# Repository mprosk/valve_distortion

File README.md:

# Valve Distortion
Eurorack format reimplementation of the Safety Valve from Look Mum No Computer

## Assembly Instructions

**Step 1:** Solder all resistors and diodes. Resistor values are marked on the silkscreen. **Be sure to get the correct orientation of the diodes!**

**Step 2:** Solder the ceramic capacitors. Ceramic capacitor values are marked on the silkscreen, *with the exception of 0.1uF / 100nF which are unlabeled*

**Step 3:** Solder the electrolytic capacitors. Capacitor values are marked on the silkscreen. **Be sure to get the correct polarity of the capacitors!** The white silkscreen fill indicates the negative leg of the capacitor. Capacitors should be folded down as shown above.

**Step 4:** Solder the ICs, transistor, trim pot, and 10pin power connector. **Be sure to get the correct orientation of the ICs!** Match the U shaped indent on the chip to the marking on the IC. The trim pot should be mounted sideways as shown above. The power connector should be mounted on the back of the PCB. **Make sure to get the correct orientation of the connector housing!**

**Step 5:** Place the switches, potentiometers, red 5mm LED, jacks, and tube in their respective locations in the PCB **but do not solder them yet!** First, place the faceplate over the controls and screw on the mounting hardware for each component. Note that due to slight hight differences between the parts, the nuts may not screw down all the way. **Do not over-tighten the mounting hardware as this may cause unwanted flexing of the PCBs.** You can use a rubber band or similar to hold everything together while handling. Push the legs of the LED from the back so that it just sticks through the front panel. Bend the legs from the back to hold it in place. **Be sure you have the correct polarity of the LED.**

**Step 6:** Once all the mounting hardware is secured, solder the switches, tube, LED, jacks, and potentiometers in place.

**Step 7:** Push the 3mm clear LED through the hole on the back of the PCB underneath the tube. Bend the leads such that they reach their connection points and cut them to length. **Be sure you have the correct polarity of the LED!** Solder the LED in place

**Step 8:** Put the knobs on to the potentiometers

**Step 9:** Power the module up and apply a signal to the input. Adjust the trim pot such that the LED underneath the tube illuminates when there is signal but is off when there is not. Note that sometimes the EMC of the LED can get picked up by the tube and cause an audible noise. If this occurs, adjust the trim pot such that the LED does not illuminate regardless of the signal level.

**Step 10:** Enjoy your gnarly new distortion module!

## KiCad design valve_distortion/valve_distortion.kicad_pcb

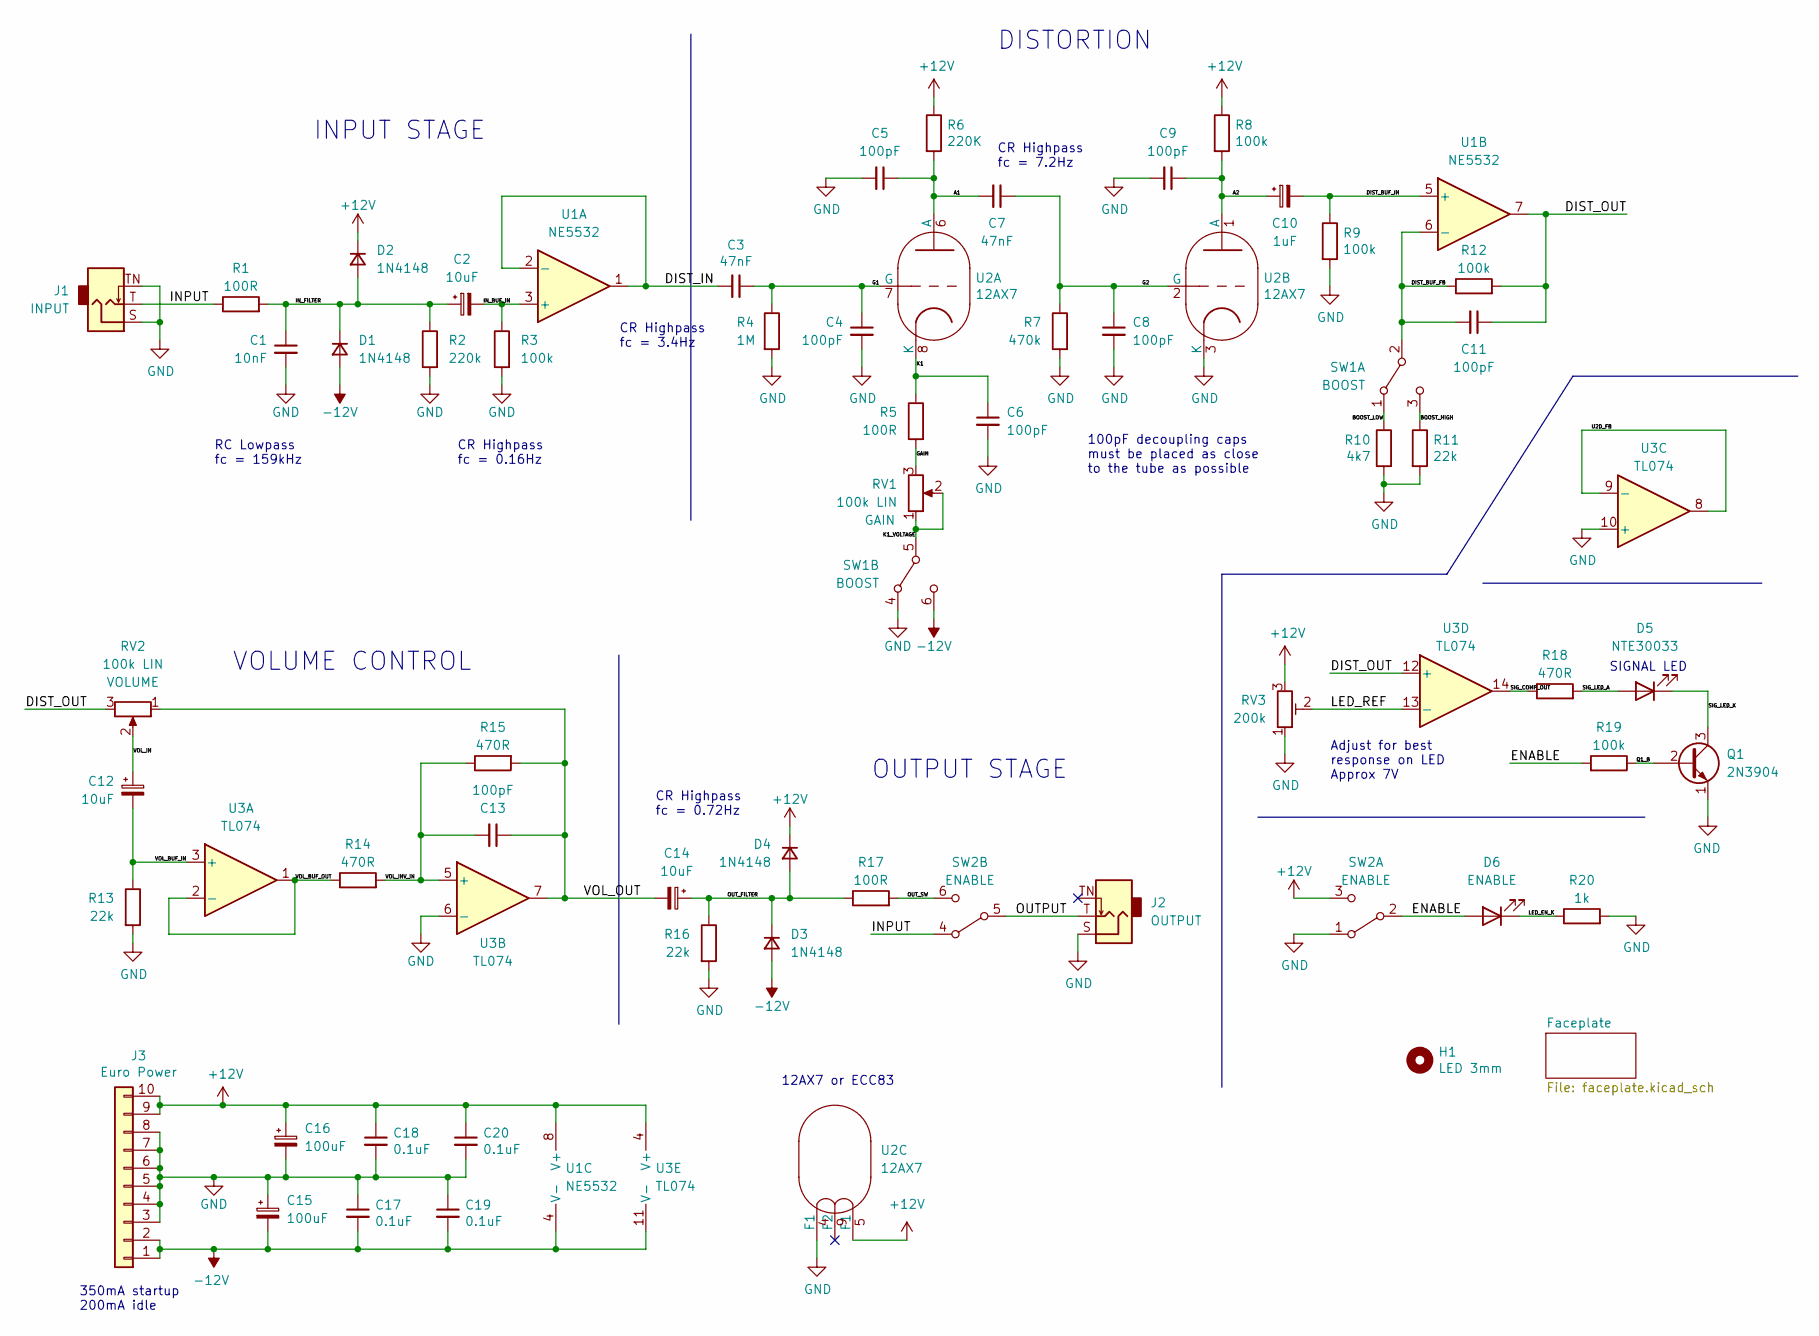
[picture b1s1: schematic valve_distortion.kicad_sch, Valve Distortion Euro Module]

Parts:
C1: 10nF; C_Disc_D4.3mm_W1.9mm_P5.00mm
C2, C12, C14: 10uF; CP_Radial_D5.0mm_P2.50mm
C3, C7: 47nF; C_Disc_D3.0mm_W1.6mm_P2.50mm
C4, C5, C6, C8, C9, C11, C13: 100pF; C_Disc_D3.0mm_W1.6mm_P2.50mm
C10: 1uF; CP_Radial_D5.0mm_P2.50mm
C15, C16: 100uF; CP_Radial_D5.0mm_P2.50mm
C17, C18, C19, C20: 0.1uF; C_Disc_D3.0mm_W1.6mm_P2.50mm
D1, D2, D3, D4: 1N4148; D_DO-34_SOD68_P7.62mm_Horizontal
D5: NTE30033; LED_D3.0mm_Clear
D6: ENABLE; LED_D5.0mm
H1: LED 3mm; Hole_LED_3mm
J1: INPUT; Jack_3.5mm_QingPu_WQP-PJ301BM
J2: OUTPUT; Jack_3.5mm_QingPu_WQP-PJ301BM
J3: Euro Power; IDC-Header_2x05_P2.54mm_Vertical
Q1: 2N3904; TO-92_Inline
R1, R5, R17: 100R; R_Axial_DIN0207_L6.3mm_D2.5mm_P10.16mm_Horizontal
R2: 220k; R_Axial_DIN0207_L6.3mm_D2.5mm_P10.16mm_Horizontal
R3, R8, R9, R12, R19: 100k; R_Axial_DIN0207_L6.3mm_D2.5mm_P10.16mm_Horizontal
R4: 1M; R_Axial_DIN0207_L6.3mm_D2.5mm_P10.16mm_Horizontal
R6: 220K; R_Axial_DIN0207_L6.3mm_D2.5mm_P10.16mm_Horizontal
R7: 470k; R_Axial_DIN0207_L6.3mm_D2.5mm_P10.16mm_Horizontal
R10: 4k7; R_Axial_DIN0207_L6.3mm_D2.5mm_P10.16mm_Horizontal
R11, R13, R16: 22k; R_Axial_DIN0207_L6.3mm_D2.5mm_P10.16mm_Horizontal
R14, R15, R18: 470R; R_Axial_DIN0207_L6.3mm_D2.5mm_P10.16mm_Horizontal
R20: 1k; R_Axial_DIN0207_L6.3mm_D2.5mm_P10.16mm_Horizontal
RV1, RV2: 100k LIN; Potentiometer_TT_P0915N
RV3: 200k; Potentiometer_Trim_Horizontal
SW1: BOOST; Switch_DPDT
SW2: ENABLE; Switch_DPDT
U1: NE5532; DIP-8_W7.62mm
U2: 12AX7; Valve_ECC-83-1
U3: TL074; DIP-14_W7.62mm

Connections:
+12V: C16.1, C18.1, C20.1, D2.1 (K), D4.1 (K), J3.9, J3.10, R6.1, R8.1, RV3.3, SW2.3 (C), U1.8 (V+), U2.5 (F1), U3.4 (V+)
-12V: C15.2, C17.2, C19.2, D1.2 (A), D3.2 (A), J3.1, J3.2, SW1.6 (C), U1.4 (V-), U3.11 (V-)
/A1: C5.1, C7.2, R6.2, U2.6 (A)
/A2: C9.1, C10.1, R8.2, U2.1 (A)
/BOOST_HIGH: R11.1, SW1.3 (C)
/BOOST_LOW: R10.1, SW1.1 (A)
/DIST_BUF_FB: C11.2, R12.1, SW1.2 (B), U1.6 (-)
/DIST_BUF_IN: C10.2, R9.1, U1.5 (+)
/DIST_IN: C3.2, U1.1, U1.2 (-)
/DIST_OUT: C11.1, R12.2, RV2.3, U1.7, U3.12 (+)
/ENABLE: D6.2 (A), R19.2, SW2.2 (B)
/G1: C3.1, C4.1, R4.1, U2.7 (G)
/G2: C7.1, C8.1, R7.1, U2.2 (G)
/GAIN: R5.2, RV1.3
/INPUT: J1.T, R1.1, SW2.4 (A)
/IN_BUF_IN: C2.2, R3.1, U1.3 (+)
/IN_FILTER: C1.1, C2.1, D1.1 (K), D2.2 (A), R1.2, R2.1
/K1: C6.1, R5.1, U2.8 (K)
/K1_VOLTAGE: RV1.1, RV1.2, SW1.5 (B)
/LED_EN_K: D6.1 (K), R20.1
/LED_REF: RV3.2, U3.13 (-)
/OUTPUT: J2.T, SW2.5 (B)
/OUT_FILTER: C14.1, D3.1 (K), D4.2 (A), R16.1, R17.1
/OUT_SW: R17.2, SW2.6 (C)
/Q1_B: Q1.2 (B), R19.1
/SIG_COMP_OUT: R18.1, U3.14
/SIG_LED_A: D5.2 (A), R18.2
/SIG_LED_K: D5.1 (K), Q1.3 (C)
/U2D_FB: U3.8, U3.9 (-)
/VOL_BUF_IN: C12.2, R13.1, U3.3 (+)
/VOL_BUF_OUT: R14.1, U3.1, U3.2 (-)
/VOL_IN: C12.1, RV2.2
/VOL_INV_IN: C13.2, R14.2, R15.1, U3.5 (+)
/VOL_OUT: C13.1, C14.2, R15.2, RV2.1, U3.7
GND: C1.2, C4.2, C5.2, C6.2, C8.2, C9.2, C15.1, C16.2, C17.1, C18.2, C19.1, C20.2, J1.S, J1.TN, J2.S, J3.3, J3.4, J3.5, J3.6, J3.7, J3.8, Q1.1 (E), R2.2, R3.2, R4.2, R7.2, R9.2, R10.2, R11.2, R13.2, R16.2, R20.2, RV3.1, SW1.4 (A), SW2.1 (A), U2.3 (K), U2.4 (F1), U3.6 (-), U3.10 (+)

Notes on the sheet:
CR Highpass fc = 0.16Hz
VOLUME CONTROL
CR Highpass fc = 3.4Hz
12AX7 or ECC83
Adjust for best response on LED Approx 7V
DISTORTION
RC Lowpass fc = 159kHz
CR Highpass fc = 0.72Hz
INPUT STAGE
100pF decoupling caps must be placed as close to the tube as possible
OUTPUT STAGE
CR Highpass fc = 7.2Hz
350mA startup 200mA idle
SIGNAL LED

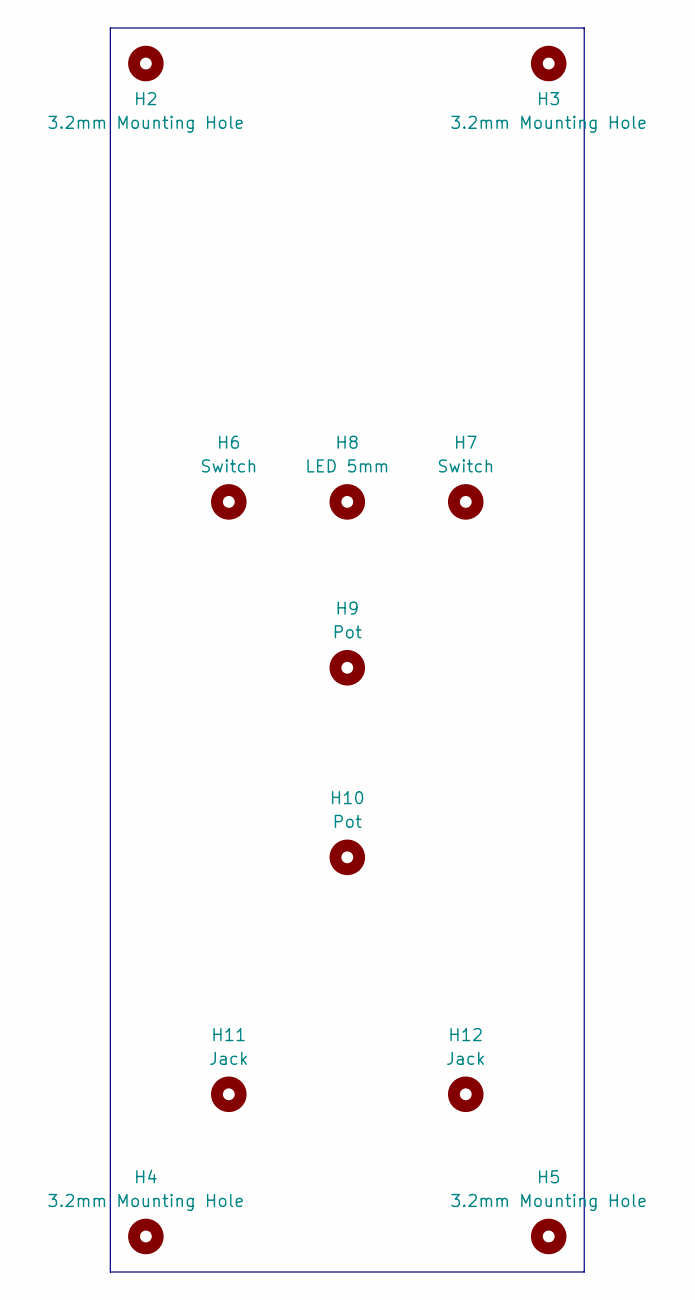
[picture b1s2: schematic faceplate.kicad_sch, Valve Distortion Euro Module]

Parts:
H2, H3, H4, H5: 3.2mm Mounting Hole; MountingHole_3.2mm_M3
H6, H7: Switch; Hole_Toggle_Switch
H8: LED 5mm; Hole_LED_5mm
H9, H10: Pot; Hole_Pot
H11, H12: Jack; Hole_Jack_3.5mm

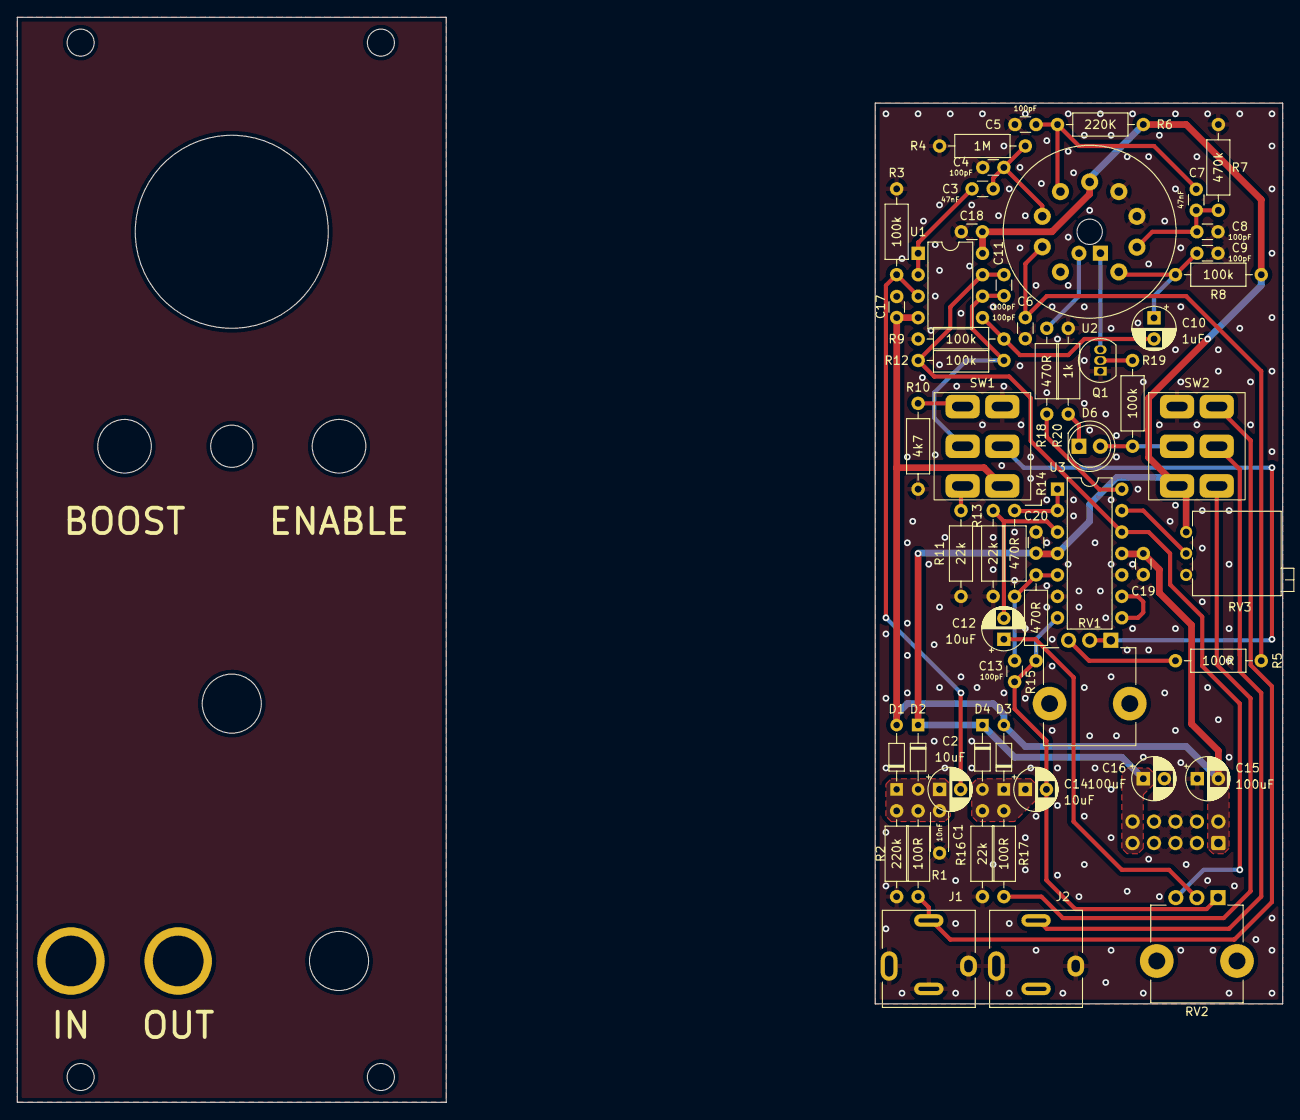
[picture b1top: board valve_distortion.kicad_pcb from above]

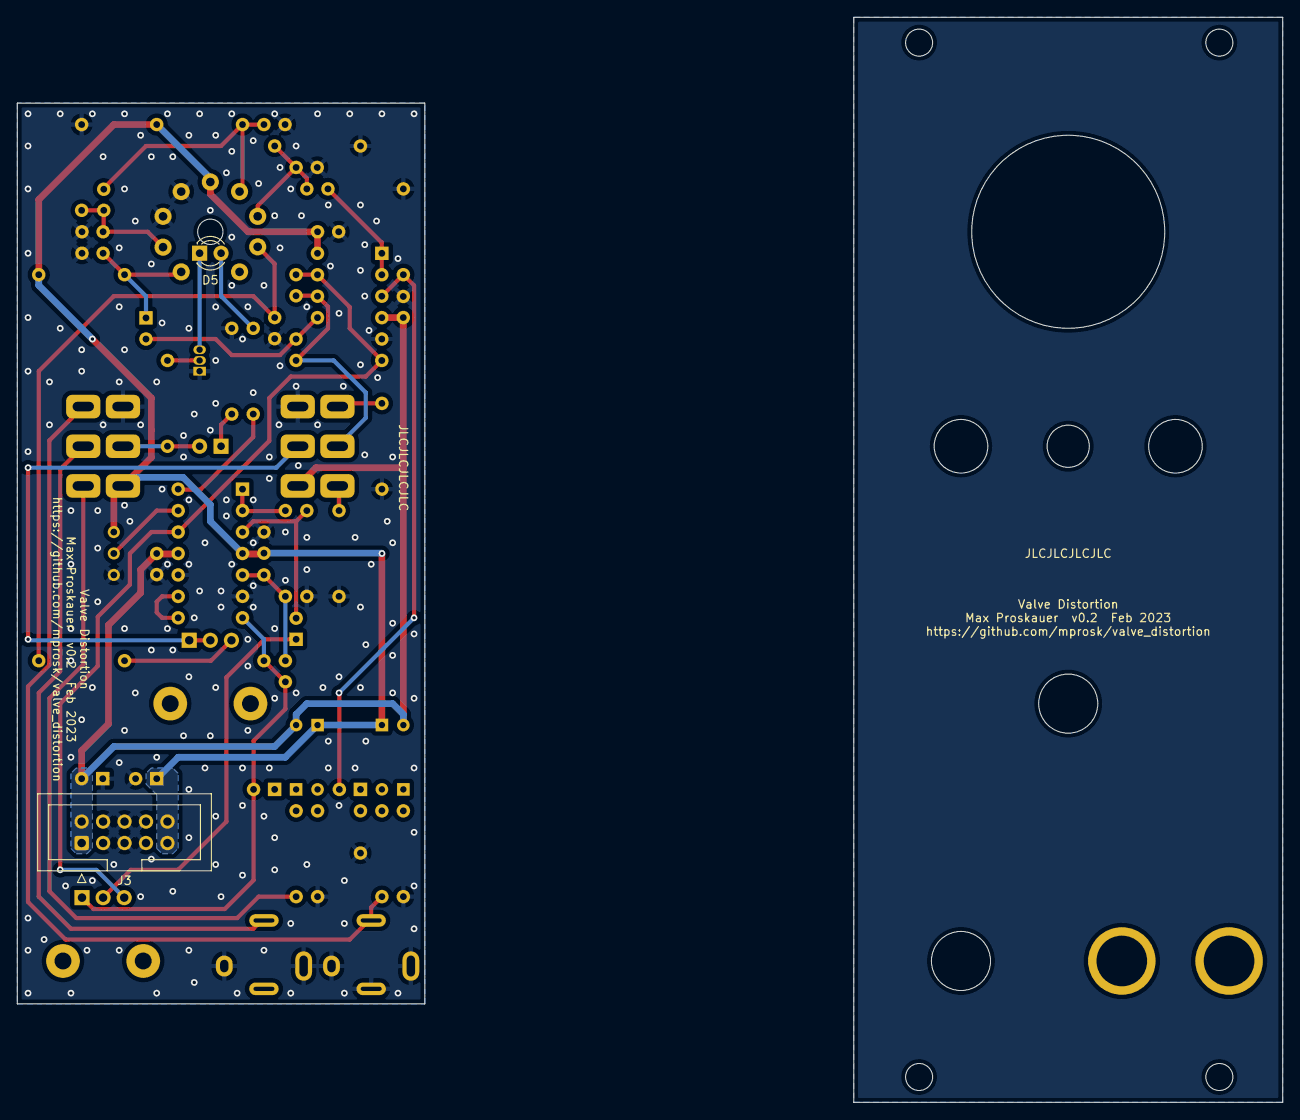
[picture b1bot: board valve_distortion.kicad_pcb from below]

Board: 2 copper layers, 48.3 x 106.7 mm, 70 parts (2 on the bottom side), 35 nets.

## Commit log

2022-06-03 Import files from deprecated repo and update to kicad6
2023-01-21 Add complete files for valve distortion euro module
2023-02-15 Fix rev1 pcb issues
2023-02-15 Add images
2023-02-15 Add images to readme
2023-02-15 Fix image link
2024-01-21 Add assembly instructions to README
